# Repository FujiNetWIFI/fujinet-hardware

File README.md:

# FujiNet Hardware

Hardware design files for FujiNet Retro Computer WiFi Adapter

# License

This project is released under the CERN OHL v2.0.

# Notice

Licensees must place a link to the FujiNet project github site, github.com/FujiNetWIFI OR fujinetwifi.github.io, on any product produced using these designs. Using the PCB silk screen layer is recommended for the link and is already provided on released designs.

# Certification

FujiNet hardware is certified open source by [OSHWA](https://oshwa.org). Certification details are available in the [certification directory](https://certification.oshwa.org/us000651.html) under the UID US000651.

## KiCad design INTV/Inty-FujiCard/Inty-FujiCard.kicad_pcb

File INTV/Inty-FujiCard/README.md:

# Inty-FujiCard

FujiNet for the Intellivision, on one cartridge: Yannick Erb's production design (EasyEDA project PINTY-FUJI-CARD, PCB v1.1, 2026-11-04), converted to KiCad in the structure of the other console bring-ups.
- **RP2354A:** serves the CP1610's bus (`fujinet-firmware/pico/intellivision`, board `fujicard`). AD0-15, MSYNC, BDIR, BC1 and BC2 go straight from the edge to its GPIOs.
- **ESP32-S3:** the FujiNet (`fujiversal-intv`) and the RP's USB host, on the same board.
- **Also on the board:** a microSD, an SK6805 status LED, and a USB-C with a CP2102N bridge for flashing and power.

`Original/` holds Yannick's files exactly as he sent them: the EasyEDA PCB (JSON), an Altium ASCII export, his gerbers and drills, BOM and pick-and-place. Everything else is generated from them (`tools/`).

**Status (2026-11-05): converted, every gate passing. The copper, masks, paste, drills and silkscreen equal Yannick's gerbers; his BOM and placements are carried over unchanged.**
- **Board:** 2 layers, 58.2 x 60.0 mm, 1.6 mm. Yannick's layout, unchanged. His EasyEDA files had no schematic: the schematic here is drawn from the board's netlist.
- **Firmware:** the netlist matches `fujicard.h` and `fujiversal-intv.h` on every bus and S3 pin. The mismatches are listed under *Firmware*.
- **Before ordering:** see *Known limits / review*. The paste layers open the gold fingers, and three lines were out of stock on 2026-11-05.

| Check (2026-11-05) | Result |
|---|---|
| `tools/audit/gerber_equiv.py`: our PCBWay zip against Yannick's gerber zip, rasterised at 40 px/mm and XOR-ed | F.Cu, B.Cu, F/B.Mask, F/B.Paste, outline: identical (nothing left after a 50 um opening); silkscreen graphics identical, all 42 visible texts centred within 0.05 mm of his; 160 plated and 6 unplated holes, all his |
| `tools/board_netlist.py --check`: `tools/design.py` against the board's own netlist | 76 nets, 78 parts, every unconnected pad NC; Yannick's net names kept |
| Drawing checks (`gen_sch.py`) and netlist parity (kicad-cli netlist against `design.py`, names included) | every sheet wired; 0 crossings on 4 sheets, 1 on `usb` (esptool's auto-program pair); 76 / 76 nets |
| KiCad ERC, all severities | 0 errors, 0 warnings |
| `tools/check_nets.py`: the netlist against `fujicard.h`, `pintycard.h`, `fujiversal-intv.h` (fujinet-firmware `origin/master`) | 72 checks, 0 failed; 8 NOTE lines (*Firmware*) |
| `tools/sync_board.py`: schematic -> board, names and fields only | copper hash unchanged |
| `tools/audit/check_drc.py`: KiCad DRC + schematic parity on the saved fills (kicad-cli; again through the KiCad MCP) | 0 errors, 0 unconnected, 0 parity issues; 101 warnings, all from Yannick's footprints (*Design rules*) |
| `tools/audit/check_fab.py`: the JLCPCB / PCBWay packages against his BOM and pick-and-place | BOM = his 31 lines / 70 parts with his LCSC codes and MPNs; CPL = his placements (worst 0.005 mm, every rotation); the zips |

## What the conversion changed

KiCad 10.0.8's EasyEDA importer (`pcbnew.PCB_IO_MGR.EASYEDA`) reads the JSON. `tools/convert.py` keeps what it gets right and fixes what it gets wrong. Each fix is proven against Yannick's gerbers:
1. **The GND pours' holes.** EasyEDA stores each pour's fill with its clearance holes, and the importer drops the holes. As imported, the B.Cu pour covered 31 signal tracks (230 mm2 of copper that is not on his board), and the F.Cu pour filled 129 clearances. The fills are rebuilt from the JSON.
2. **Paste and silkscreen drawn inside footprints.** The importer drops these shapes: 142 paste openings and 13 silkscreen marks (polarity bars, pin-1 dots). Their pads carry EasyEDA's "no paste of its own" value (-393.7 x 10 mil, imported as a -100 mm margin). They are restored; those 138 pads have no F.Paste of their own.
3. **Text.** The importer shows every value and reference; the JSON hides all values and 40 references, and its visibility flags are applied. KiCad anchors each text where EasyEDA's starts, so every text sat 0.2-1.4 mm off; each is moved so its strokes are centred on EasyEDA's. The font is KiCad's.
4. **3D models.** The importer offsets each EasyEDA model as if its origin were its solids' box centre and bottom. EasyEDA places them by that box, and several are not centred on their origin: the microSD socket sat 29 mm away and under the board. `tools/fetch_models.py` normalises each model (`3d/README.md`).
5. **Solid regions** (the 386 teardrops and copper shapes) become filled copper polygons with their nets, not zones, so no refill can redraw them. Two that EasyEDA drew twice are kept once.
6. **Housekeeping:**
   - KiCad's own layer names.
   - The 23 footprints go into `Inty-FujiCard.pretty`.
   - The designators KiCad cannot annotate are numbered (table below).
   - The 3D models are bundled.
   - The crystal's no-fill keep-out is 10 um smaller: EasyEDA's pour touched it.
   - UUIDs are fixed, so a rerun diffs clean.

**Never refill the zones.** The two GND pours are EasyEDA's own fills. A refill (B in pcbnew, `--refill-zones`, `--check-zones`) replaces them with KiCad's. `tools/audit/gerber_equiv.py` would then report the difference.

| Yannick's | Here | | Yannick's | Here |
|---|---|---|---|---|
| BOOT | SW1 | | GND (test pad) | TP1 |
| RESET | SW2 | | TX | TP2 |
| RP-BOOT | SW3 | | RX | TP3 |
| RP-RUN | SW4 | | SWD | TP4 |
| LED | D6 | | SWCLK | TP5 |
| USB | J1 | | Hole_gge2670 / 2700 | H1 / H2 |

The silkscreen still reads BOOT, RESET, RP-BOOT, RP-RUN, LED, USB, GND, TX, RX, SWD and SWCLK: each label is kept as board text, grouped with its part. Every other designator is his.

## Sheets

Drawn with the FujiNet-ColecoVision / O2 / Arcadia toolkit:
- **Wires only:** every connection on a sheet is a wire.
- **Rails:** rails are power symbols (`GND`, `VSYS`, `VBUS`, `VIN`, `3V3`, `1V1`).
- **Between sheets:** sheets join only through hierarchical labels, wired on the root's block diagram.

| Page | Sheet | Contents |
|---|---|---|
| 1 | root | the block diagram: rp-core <-> fujinet (USB_DP / USB_DM, RUN_CTL, BOOTSEL_CTL), fujinet <-> usb (S3_TXD / S3_RXD, S3_EN, S3_IO0); notes |
| 2 | `cart-bus` | the 44-finger edge and the RP2354A's GPIO unit row for row; the console reset (GP20, R13, Q1), the ECS audio (GP28, R5), the TX / RX pads |
| 3 | `rp-core` | the RP2354A's core unit: its supply capacitors, core regulator (L1, R6 / C19), crystal, USB 27R pair, QSPI_SS / RP-BOOT / Q3, RUN / RP-RUN / Q4, SWD pads |
| 4 | `fujinet` | ESP32-S3-WROOM-1-N16R8, EN RC and RESET, BOOT, microSD with the YC158 pull-ups, SK6805 |
| 5 | `usb` | USB-C, ESD5Z diodes, CP2102N, esptool's auto-program pair (UMH3N) |
| 6 | `power` | the SS34 diode-OR (VSYS, VBUS -> VIN), the AP63203 buck (3V3), PWR_FLAGs, the holes |

## Edge connector

44 contacts in two rows of 22 at 2.54 mm. Yannick's footprint numbers them A1-A22 on the component face and B1-B22 behind, left to right, seen from the component face with the contacts down. Finger A(k) is INTV pin 46 - 2k, and B(k) is pin 45 - 2k: even pins in front, odd behind.

| Pin | Finger | Signal | Goes to | Pin | Finger | Signal | Goes to |
|---|---|---|---|---|---|---|---|
| 1 | B22 | GND | GND | 2 | A22 | NC | - |
| 3 | B21 | /MSYNC | GP21 | 4 | A21 | NC | - |
| 5 | B20 | D7 | GP7 | 6 | A20 | EXT_AUDIO | R5 from GP28 |
| 7 | B19 | D8 | GP8 | 8 | A19 | GND | GND |
| 9 | B18 | D6 | GP6 | 10 | A18 | GND | GND |
| 11 | B17 | D9 | GP9 | 12 | A17 | /RESET | Q1 (GP20 via R13) |
| 13 | B16 | D5 | GP5 | 14 | A16 | NC | - |
| 15 | B15 | D10 | GP10 | 16 | A15 | NC | - |
| 17 | B14 | D4 | GP4 | 18 | A14 | NC | - |
| 19 | B13 | D11 | GP11 | 20 | A13 | GND | GND |
| 21 | B12 | D3 | GP3 | 22 | A12 | GND | GND |
| 23 | B11 | D12 | GP12 | 24 | A11 | GND | GND |
| 25 | B10 | D13 | GP13 | 26 | A10 | GND | GND |
| 27 | B9 | D2 | GP2 | 28 | A9 | GND | GND |
| 29 | B8 | D14 | GP14 | 30 | A8 | NC | - |
| 31 | B7 | D1 | GP1 | 32 | A7 | PASS_A | joined to pin 42 |
| 33 | B6 | D0 | GP0 | 34 | A6 | PASS_B | joined to pin 40 |
| 35 | B5 | D15 | GP15 | 36 | A5 | PASS_C | joined to pin 38 |
| 37 | B4 | BDIR | GP22 | 38 | A4 | PASS_C | joined to pin 36 |
| 39 | B3 | BC2 | GP27 | 40 | A3 | PASS_B | joined to pin 34 |
| 41 | B2 | BC1 | GP26 | 42 | A2 | PASS_A | joined to pin 32 |
| 43 | B1 | +5V | VSYS -> D1 | 44 | A1 | GND | GND |

The pinout is the attic FujiNet-INTV-Rev0's edge, traced from the PiNTY CARD's gerbers. The firmware's bus map agrees on every finger (`tools/check_nets.py` keeps its own copy of both).

## RP2354A pin map

| GPIO | Net | Goes to |
|---|---|---|
| 0-15 | GPIO00-15 | the edge's D0-D15 (`MI_AD0_PIN` 0), straight |
| 16 / 17 | GPIO16 / 17 | test pads TP2 (silk TX) / TP3 (silk RX) |
| 18, 19, 23, 24, 25, 29 | - | not connected |
| 20 | GPIO20 | R13 -> Q1: high pulls the console's /RESET (pin 12) low (`MI_RST_PIN`) |
| 21 / 22 | GPIO21 / 22 | MSYNC / BDIR, straight |
| 26 / 27 | GPIO26 / 27 | BC1 / BC2, straight |
| 28 | PWM | R5 1k -> EXT_AUDIO (pin 6, the ECS audio; `pintycard.h` `MI_AUDIO_PIN`) |
| QSPI | QSPI_SS | the BOOTSEL strap (R12 10k up; RP-BOOT / Q3 through R11 1k); the flash is in the package, the other QSPI pins are not connected |
| USB | USB_D+ / USB_D- | 27R -> the ESP32-S3's IO20 / IO19 (the S3 is the host) |
| RUN | RUN | R14 10k up; RP-RUN (SW4); Q4 |

## ESP32-S3 pin map

`include/pinmap/fujiversal-intv.h`:

| S3 pin | Net | Goes to |
|---|---|---|
| IO19 / IO20 | USB_DM / USB_DP | the RP2354A's USB through its 27R |
| IO38 / 39 / 40 / 41 | SD_MOSI / SCK / MISO / CS | microSD (SPI); 10k pull-ups (RN1) on CS, DO, DI, DAT1, DAT2; card detect not connected |
| IO48 | LED_STRIP | 330R -> SK6805-EC20 (on 3V3) |
| TXD0 / RXD0 | S3_TXD / S3_RXD | CP2102N RXD / TXD |
| IO4 / IO5 | RUN_CTL / BOOTSEL_CTL | 1k -> Q4 / Q3: high pulls the RP's RUN / QSPI_SS low |
| EN / IO0 | S3_EN / S3_IO0 | 10k / 1 uF and RESET (SW2); BOOT (SW1), 100 nF, 10k up; the auto-program pair |

## Power

| Rail | Source | Feeds |
|---|---|---|
| `VSYS` | edge pin 43, the console's +5V | D1 (SS34) -> VIN |
| `VBUS` | USB-C | D2 (SS34) -> VIN; the CP2102N's VBUS sense (22.1k / 47.5k) |
| `VIN` | the higher of the two, less a Schottky drop | C29 100 uF, C25 10 uF; the AP63203 |
| `3V3` | AP63203, 3.3 V / 2 A buck (4.7 uH) | everything: the RP2354A (IOVDD, VREG_VIN, ADC, USB, QSPI), the ESP32-S3, the CP2102N, the microSD, the SK6805 |
| `1V1` | the RP2354A's core regulator (L1 3.3 uH) | the RP's DVDD |

Neither source can back-feed the other: a cart on USB never powers a console that is off.

## Design rules

The Board Setup minimums (`tools/rules.json`) are the lowest values Yannick's copper needs. `Inty-FujiCard.kicad_dru` holds everything else to JLCPCB's standard 1-2 layer figures (0.127 mm space, 0.45 / 0.2 mm via, 0.125 mm ring, 0.3 mm to the edge). The measured exceptions:
- **Spacing:** 6 spots at 0.107-0.121 mm, in the RP2354A's and the CP2102N's fan-out (QFNs at 0.4 / 0.5 mm pitch). His EasyEDA rule there is 0.1016 mm.
- **Vias:** 151 are 0.457 / 0.254 mm, a 0.1015 mm ring (EasyEDA's 18 / 10 mil). The other 5 are 0.62 / 0.31 mm.
- **Hole clearance:** the USB-C's own pads sit 0.171-0.213 mm from its locating pegs (the connector's footprint). One B.Cu track (GPIO09) passes 0.243 mm from GPIO08's via.
- **Edge clearance:** the two GND pours stop 0.259 mm from the outline's centre line.
- **Placement:** C9, C10, C13 and C19 are inside the RP2354A's courtyard, and R3 overlaps L1's (EasyEDA courtyards).
- **Pad 23:** the CP2102N's GND pad 23 reaches the pour by one spoke.

The 101 DRC warnings are all his footprints' (`tools/audit/check_drc.py` fails on any other):
- 47 `lib_footprint_mismatch`: EasyEDA placed each instance with its own 0.1-0.2 um rounding and fab-text angle; the library holds the first.
- 39 `silk_overlap`: polarity bars and pin-1 dots over the parts' own outlines.
- 10 `silk_edge_clearance`: the USB-C, the S3 and the microSD outlines at the board edge.
- 4 `silk_over_copper`: the USB-C outline over its shell legs.
- 1 `track_dangling`: a zero-length 3V3 dot on B.Cu, which is in his gerbers too.

## Parts

Every part is Yannick's, with his LCSC code (`Inty-FujiCard-BOM.csv` has MPN, manufacturer and LCSC for every line). Run `python3 tools/audit/sourcing.py` on order day.

**Stock (2026-11-05, `docs/sourcing.md`):** 31 lines, about USD 11.59 of parts per board. Three lines are short at JLCPCB:
- **U1 RP2354A** (C41378174): JLCPCB 0, LCSC 0.
- **U2 AP63203WU-7** (C780769): JLCPCB 0, LCSC 0.
- **RN1 YC158TJR-0710KL** (C309679): JLCPCB 1, LCSC 0.

Consign them, use JLC Global Sourcing, or order from PCBWay, which sources by MPN. **C29** (Lelon VE-101M1ATR-0505, C134722) is marked `stop_product` at LCSC, with 408 left at JLCPCB. Any substitute is Yannick's call.

## Ordering

- **JLCPCB:** `exports/jlcpcb/ORDER-JLCPCB.md`. `BOM-JLCPCB.csv` and `CPL-JLCPCB.csv` equal his files: his footprints are LCSC's own, so no rotation table applies. The zip carries the order-number text on the back silkscreen.
- **PCBWay:** `exports/pcbway/ORDER-PCBWay.md`, turnkey by MPN (`BOM-PCBWay.csv`), `Centroid-PCBWay.csv`, `Assembly-top.pdf`.

Yannick's files give no order options. The finish, hard-gold fingers and bevel in the ORDER files are the house recommendation for a cartridge edge: confirm them with him.

## Firmware (not changed here)

`tools/check_nets.py` reports these as NOTE lines:
1. **`fujicard.h` names pins this board does not connect:**
   - `MI_LED_PIN` 25 (no RP LED here).
   - `MI_DBG_UART_TX_PIN` 24: the TX / RX pads are GP16 / GP17.
   - `FUJI_SELFTEST_TRIGGER_PIN` 23.
   
   Its comment says "No PCB pin map is committed yet": this board is one.
2. **RUN / BOOTSEL polarity.** The S3 reaches the RP's RUN and QSPI_SS through NPNs (Q4, Q3), so IO4 / IO5 must be driven **high** to assert. `fnPicoUpdater::forceBootselViaPins()` drives them low (for a direct 1k link), so that recovery path does nothing on this board. The normal path, the USB mailbox doorbell, is unaffected.
3. **ECS audio.** GP28 is wired to EXT_AUDIO as `pintycard.h` has it (`MI_AUDIO_PIN` 28). `fujicard.h` defines no audio pin, and `fujicard.cmake` has `CONFIG_ECS_AUDIO` off.

## Known limits / review

- **Paste on the gold fingers.** His F.Paste and B.Paste open all 44 fingers, and our gerbers equal his. Ask the fab to keep the fingers out of the stencil, or confirm with Yannick how his boards were built.
- **BC1 / BC2 on GP26 / GP27.** These are the RP2350's ADC pins, not 5 V tolerant (GP0-25 are). They meet the console's lines directly, as on the PiNTY CARD.
- **Fab limits.** The spacing and via-ring exceptions above are below JLCPCB's standard 2-layer figures. Check the quote's DFM report.
- **The ESP32-S3 overhangs** the board's top edge by about 6.2 mm (the antenna). The shell must allow for it.
- **Designators.** U5 is the crystal: Yannick's designator, kept.

## Bring-up checklist

1. **Rails, with no console:** USB-C only. Check 3V3 (C4 / C22) and 1V1 (C17). The SK6805 lights.
2. **First flash of the RP:** SWD on TP4 (SWDIO), TP5 (SWCLK) and TP1 (GND), with a Raspberry Pi Debug Probe. Or hold RP-BOOT while pressing RP-RUN for the USB boot ROM; its USB reaches only the S3.
3. **The S3:** flash over the USB-C. The CP2102N and the auto-program pair drive EN and IO0.
4. **In a console, no USB:** measure VIN and 3V3 under WiFi load, then CONFIG on the TV.
5. **Console off with USB on:** confirm D1 blocks: VSYS stays at 0 V.

## Regenerating

You need KiCad 10 and Python 3 with numpy, scipy and pycairo. `check_nets.py` reads fujinet-firmware from `$FUJINET_FIRMWARE` (default `~/Workspace/fujinet-firmware`) at `$FUJINET_FIRMWARE_REF` (default `origin/master`).

```sh
tools/build_all.sh                 # schematic, ERC, check_nets, sync, DRC, exports, the fab gates (keeps the board)
CONVERT=1 tools/build_all.sh       # first re-converts Original/PCB_*.json (tools/convert.py) and its netlist
python3 tools/fetch_models.py      # re-fetch the EasyEDA 3D models into 3d/ (network)
python3 tools/audit/sourcing.py    # stock at JLCPCB and LCSC -> docs/sourcing.md (network)
```

Each source file has one job:
- `tools/convert.py`: the board and footprints, from `Original/`.
- `tools/design.py`: the circuit as written out.
- `tools/sch_layout.py`: the drawing.

Edit those, never the KiCad files.

## Provenance and licence

- **The design:** Yannick Erb, PINTY-FUJI-CARD v1.1 (EasyEDA, 2026-11-04). It grows out of his PiNTY CARD (with gtortone), which is CERN-OHL-W-2.0. **His files state no licence for this board: confirm one with him before publishing it.**
- **The conversion:**
  - `tools/`; the drawing toolkit and the serializer from FujiNet-ColecoVision / O2 / Arcadia Rev0.
  - `tools/gen_sch.py`'s RP2354A core unit and S3 symbol from FujiNet-ColecoVision Rev0.
  - The edge pinout from the attic FujiNet-INTV-Rev0.
- **The pin maps:** `fujinet-firmware` `pico/intellivision` and `include/pinmap/fujiversal-intv.h`.
- **Symbols:**
  - Official KiCad libraries (CC-BY-SA 4.0 with exception).
  - Project symbols for the edge, the RP2354A in two units, the ESP32-S3 by function, Yannick's USB-C, microSD, YC158 array and SK6805-EC20, each numbered as his footprints are.
- **Footprints:** Yannick's (LCSC / EasyEDA), as on the board.
- **3D models:** `3d/README.md`.

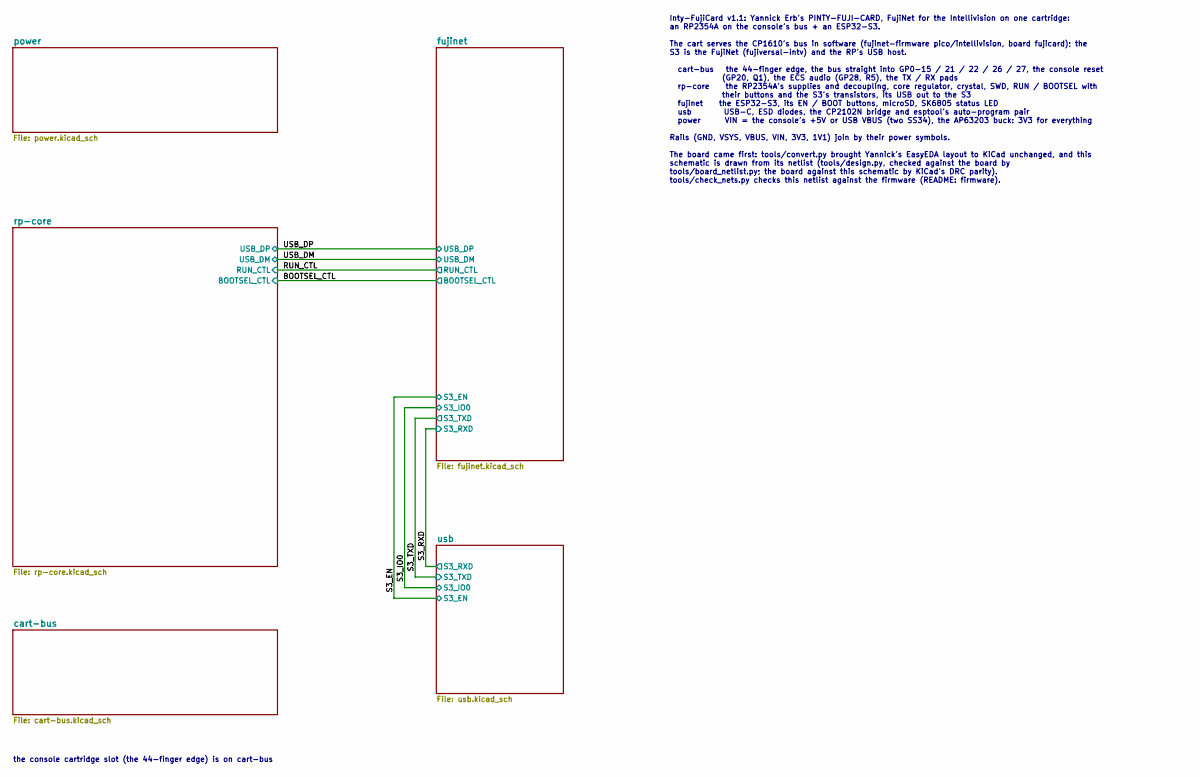
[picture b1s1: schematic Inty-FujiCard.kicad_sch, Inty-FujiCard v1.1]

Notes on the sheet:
the console cartridge slot (the 44-finger edge) is on cart-bus
Inty-FujiCard v1.1: Yannick Erb's PINTY-FUJI-CARD, FujiNet for the Intellivision on one cartridge: an RP2354A on the console's bus + an ESP32-S3. The cart serves the CP1610's bus in software (fujinet-firmware pico/intellivision, board fujicard); the S3 is the FujiNet (fujiversal-intv) and the RP's 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

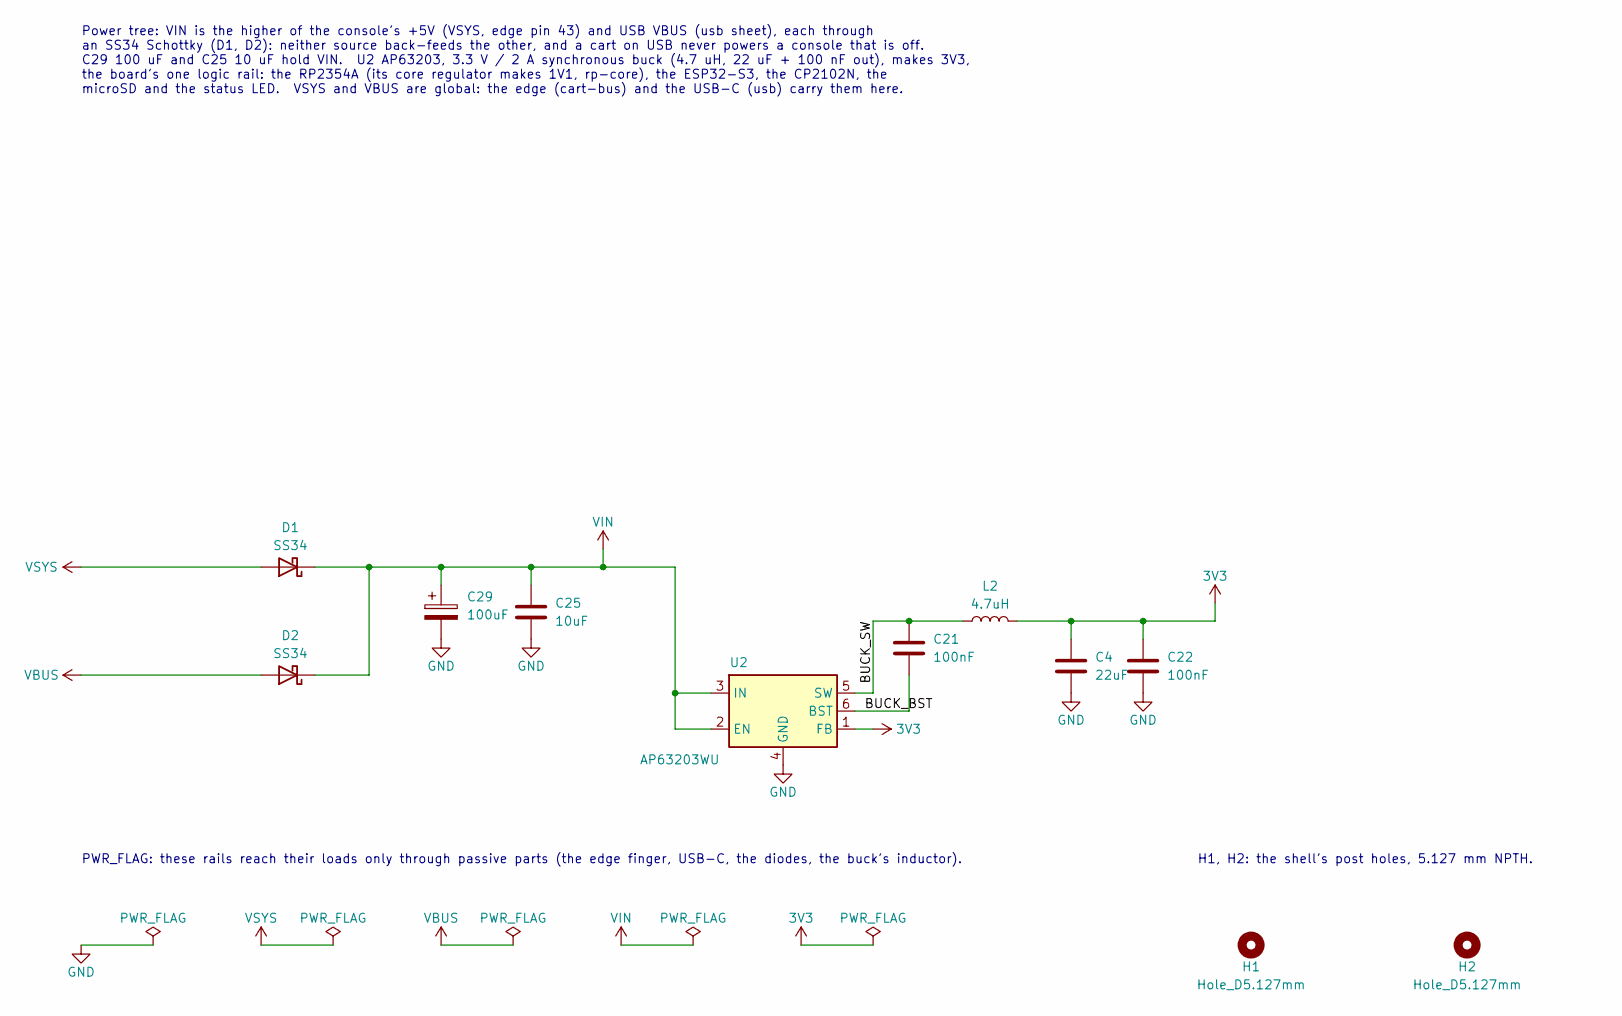
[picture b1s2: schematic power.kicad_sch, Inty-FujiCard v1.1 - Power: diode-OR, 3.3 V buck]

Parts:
C4: 22uF; C0603; MPN CL10A226MQ8NRNC; LCSC C59461
C21, C22: 100nF; C0402; MPN CL05B104KO5NNNC; LCSC C1525
C25: 10uF; C0603; MPN CL10A106KP8NNNC; LCSC C19702
C29: 100uF; CAP-SMD_BD5.0-L5.3-W5.3-RD; MPN VE-101M1ATR-0505; LCSC C134722
D1, D2: SS34; SMA_L4.3-W2.6-LS5.2-RD; MPN SS34; LCSC C8678
H1, H2: Hole_D5.127mm; Hole_D5.127mm_NPTH
L2: 4.7uH; IND-SMD_L3.0-W3.0-1; MPN YNR3015-4R7M; LCSC C340361
U2: AP63203WU; TSOT-26_L2.9-W1.6-P0.95-LS2.8-BL; MPN AP63203WU-7; LCSC C780769

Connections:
3V3: C4.2, C22.2, L2.2, U2.1 (FB); also elsewhere on the board
/power/BUCK_BST: C21.2, U2.6 (BST)
/power/BUCK_SW: C21.1, L2.1, U2.5 (SW)
GND: C4.1, C22.1, C25.1, C29.2, U2.4 (GND); also elsewhere on the board
VBUS: D2.2 (A); also elsewhere on the board
VIN: C25.2, C29.1, D1.1 (K), D2.1 (K), U2.2 (EN), U2.3 (IN)
VSYS: D1.2 (A); also elsewhere on the board

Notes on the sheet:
PWR_FLAG: these rails reach their loads only through passive parts (the edge finger, USB-C, the diodes, the buck's inductor).
H1, H2: the shell's post holes, 5.127 mm NPTH.
Power tree: VIN is the higher of the console's +5V (VSYS, edge pin 43) and USB VBUS (usb sheet), each through an SS34 Schottky (D1, D2): neither source back-feeds the other, and a cart on USB never powers a console that is off. C29 100 uF and C25 10 uF hold VIN. U2 AP63203, 3.3 V / 2 A synchronous 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

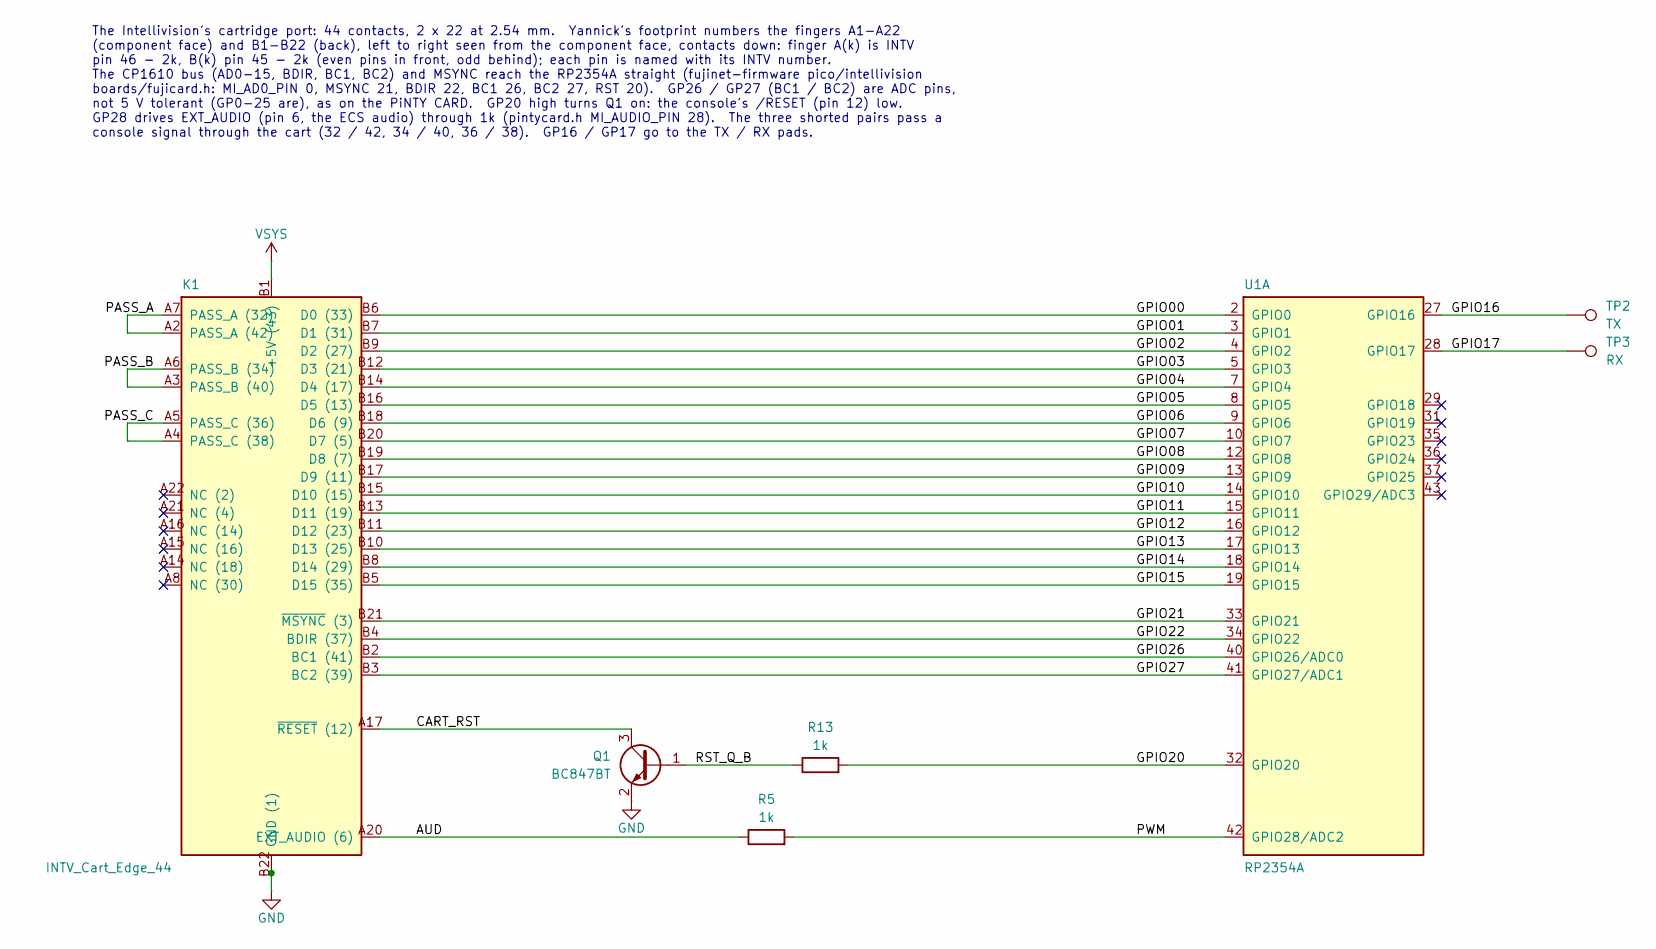
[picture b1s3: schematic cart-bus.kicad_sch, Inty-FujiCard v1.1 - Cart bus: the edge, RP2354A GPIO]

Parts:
K1: INTV_Cart_Edge_44; PCB_EDGE_CONNECTOR_22X2
Q1: BC847BT; SOT-523-3_L1.6-W0.8-P1.00-LS1.6-BR; MPN BC847BT; LCSC C5186022
R5, R13: 1k; R0402; MPN 0402WGF1001TCE; LCSC C11702
TP2: TX; TESTPOINT_PAD_D1.5MM
TP3: RX; TESTPOINT_PAD_D1.5MM
U1: RP2354A; QFN-60_L7.0-W7.0-P0.40-TL-EP3.4; MPN RP2354A; LCSC C41378174

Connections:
/cart-bus/AUD: K1.A20 (EXT_AUDIO (6)), R5.1
/cart-bus/CART_RST: K1.A17 (~RESET (12)), Q1.3 (C)
/cart-bus/GPIO00: K1.B6 (D0 (33)), U1.2 (GPIO0)
/cart-bus/GPIO01: K1.B7 (D1 (31)), U1.3 (GPIO1)
/cart-bus/GPIO02: K1.B9 (D2 (27)), U1.4 (GPIO2)
/cart-bus/GPIO03: K1.B12 (D3 (21)), U1.5 (GPIO3)
/cart-bus/GPIO04: K1.B14 (D4 (17)), U1.7 (GPIO4)
/cart-bus/GPIO05: K1.B16 (D5 (13)), U1.8 (GPIO5)
/cart-bus/GPIO06: K1.B18 (D6 (9)), U1.9 (GPIO6)
/cart-bus/GPIO07: K1.B20 (D7 (5)), U1.10 (GPIO7)
/cart-bus/GPIO08: K1.B19 (D8 (7)), U1.12 (GPIO8)
/cart-bus/GPIO09: K1.B17 (D9 (11)), U1.13 (GPIO9)
/cart-bus/GPIO10: K1.B15 (D10 (15)), U1.14 (GPIO10)
/cart-bus/GPIO11: K1.B13 (D11 (19)), U1.15 (GPIO11)
/cart-bus/GPIO12: K1.B11 (D12 (23)), U1.16 (GPIO12)
/cart-bus/GPIO13: K1.B10 (D13 (25)), U1.17 (GPIO13)
/cart-bus/GPIO14: K1.B8 (D14 (29)), U1.18 (GPIO14)
/cart-bus/GPIO15: K1.B5 (D15 (35)), U1.19 (GPIO15)
/cart-bus/GPIO16: TP2.1, U1.27 (GPIO16)
/cart-bus/GPIO17: TP3.1, U1.28 (GPIO17)
/cart-bus/GPIO20: R13.2, U1.32 (GPIO20)
/cart-bus/GPIO21: K1.B21 (~MSYNC (3)), U1.33 (GPIO21)
/cart-bus/GPIO22: K1.B4 (BDIR (37)), U1.34 (GPIO22)
/cart-bus/GPIO26: K1.B2 (BC1 (41)), U1.40 (GPIO26/ADC0)
/cart-bus/GPIO27: K1.B3 (BC2 (39)), U1.41 (GPIO27/ADC1)
/cart-bus/PASS_A: K1.A2 (PASS_A (42)), K1.A7 (PASS_A (32))
/cart-bus/PASS_B: K1.A3 (PASS_B (40)), K1.A6 (PASS_B (34))
/cart-bus/PASS_C: K1.A4 (PASS_C (38)), K1.A5 (PASS_C (36))
/cart-bus/PWM: R5.2, U1.42 (GPIO28/ADC2)
/cart-bus/RST_Q_B: Q1.1 (B), R13.1
GND: K1.A1 (GND (44)), K1.A9 (GND (28)), K1.A10 (GND (26)), K1.A11 (GND (24)), K1.A12 (GND (22)), K1.A13 (GND (20)), K1.A18 (GND (10)), K1.A19 (GND (8)), K1.B22 (GND (1)), Q1.2 (E); also elsewhere on the board
VSYS: K1.B1 (+5V (43)); also elsewhere on the board

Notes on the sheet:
The Intellivision's cartridge port: 44 contacts, 2 x 22 at 2.54 mm. Yannick's footprint numbers the fingers A1-A22 (component face) and B1-B22 (back), left to right seen from the component face, contacts down: finger A(k) is INTV pin 46 - 2k, B(k) pin 45 - 2k (even pins in front, odd behind); each 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

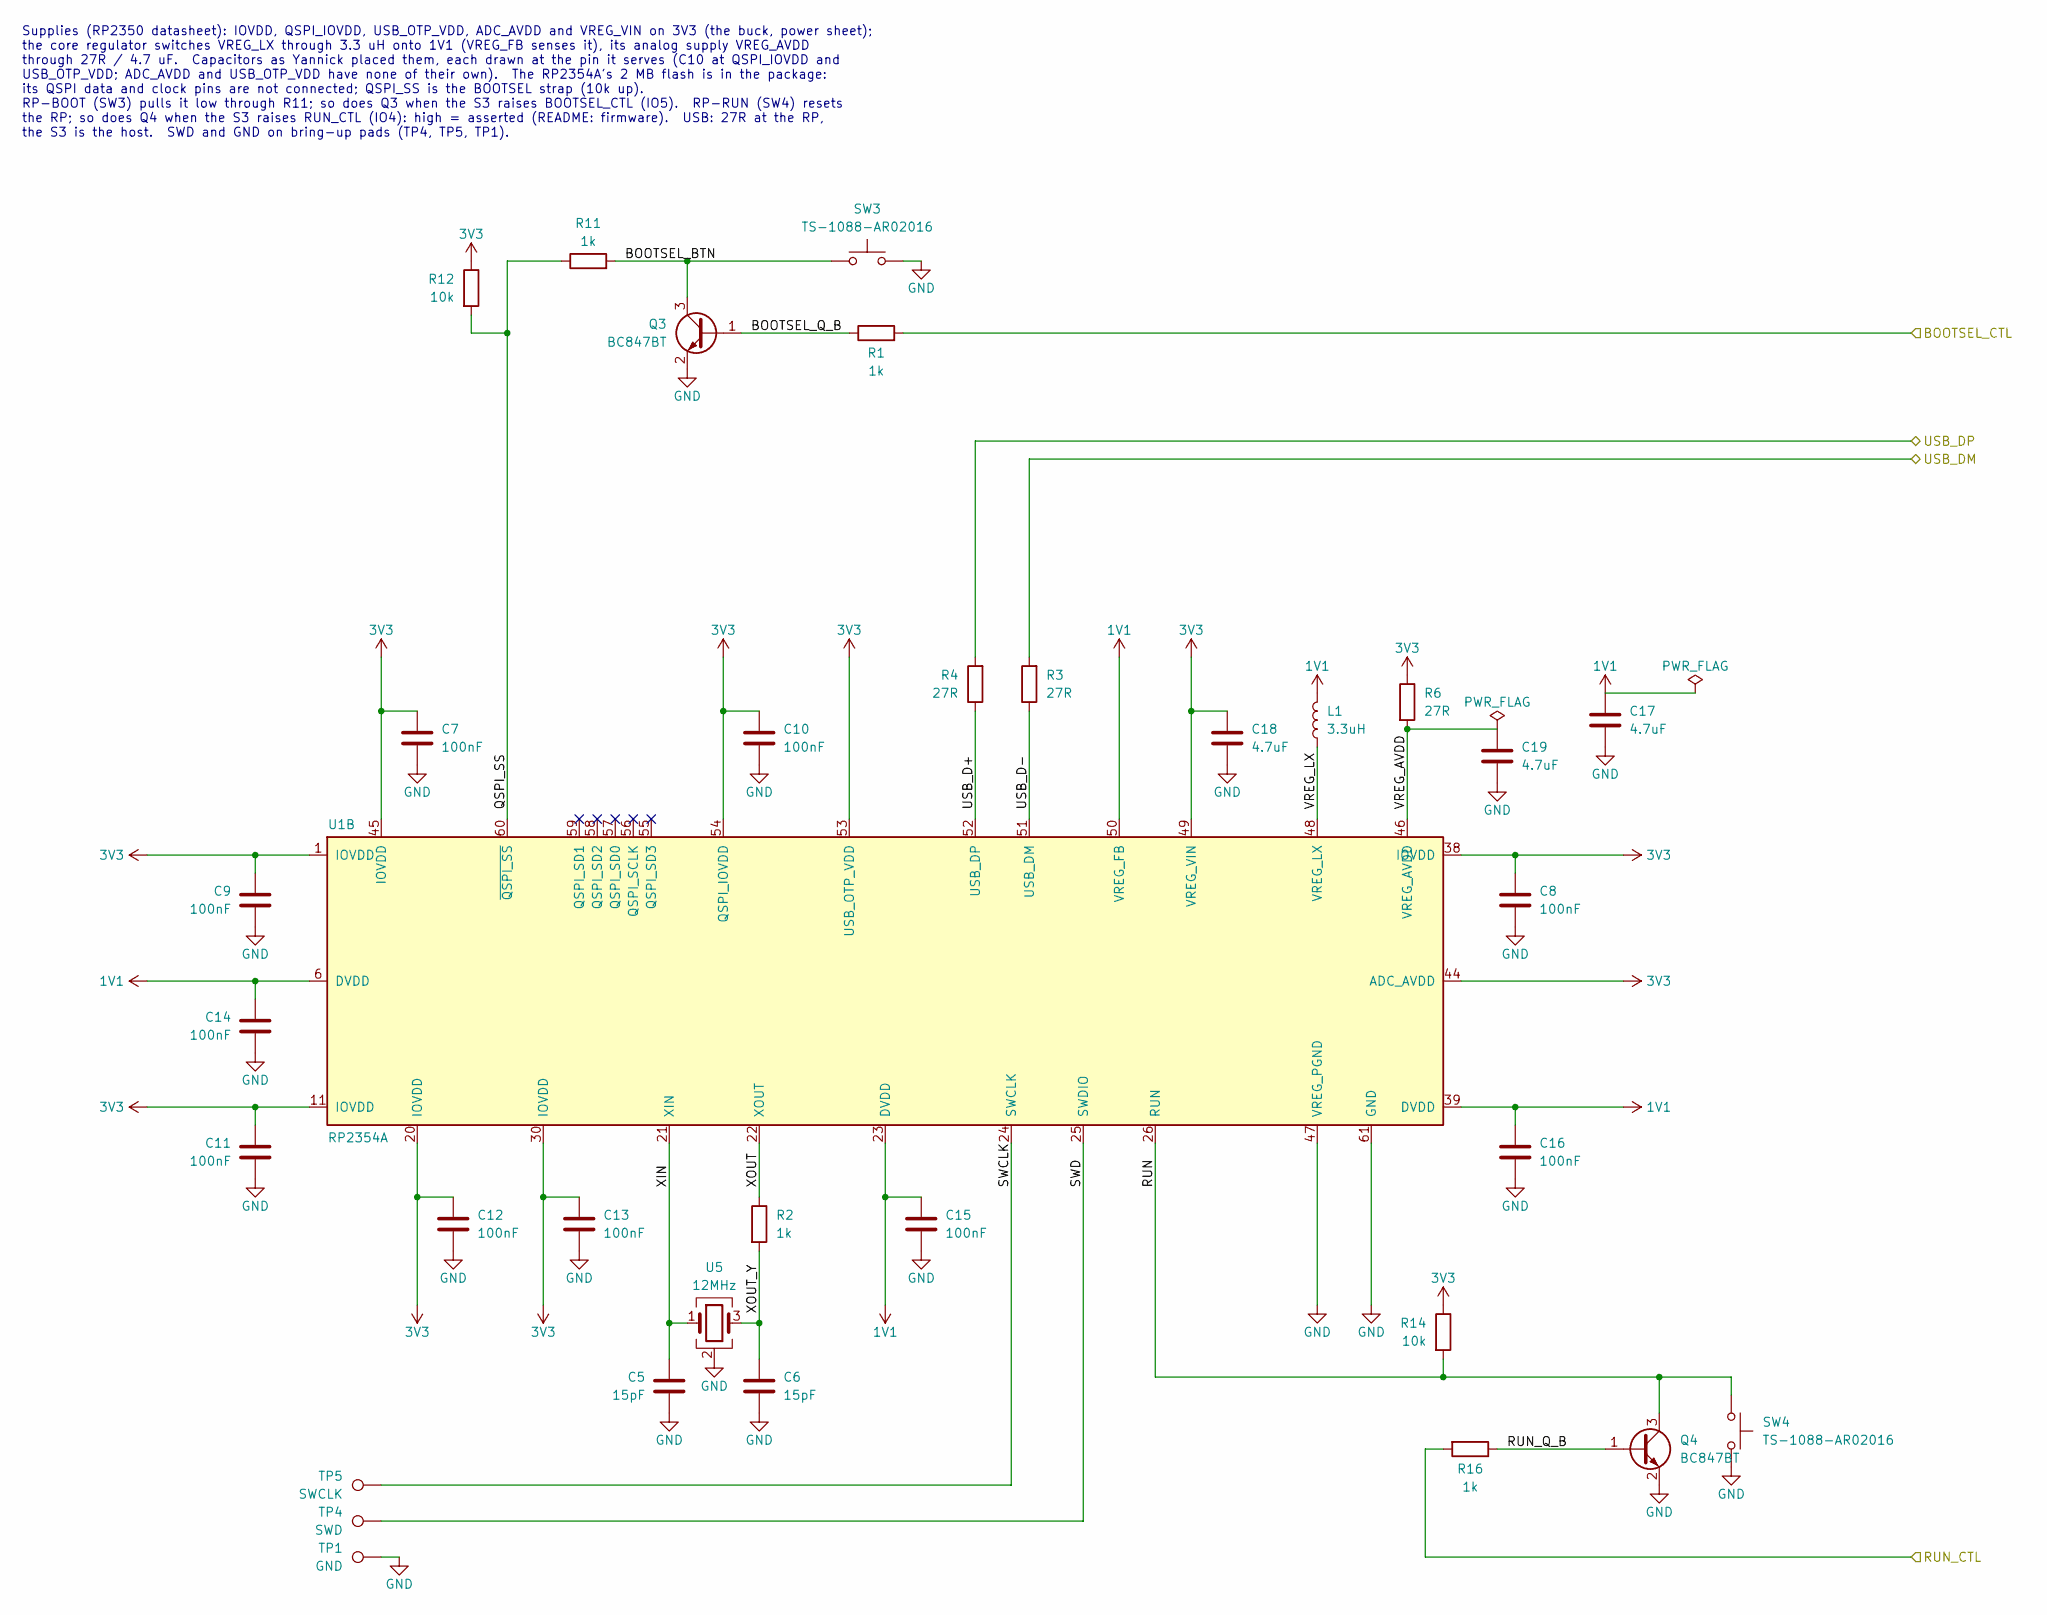
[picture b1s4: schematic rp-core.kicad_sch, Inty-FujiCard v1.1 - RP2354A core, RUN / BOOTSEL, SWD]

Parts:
C5, C6: 15pF; C0402; MPN 0402CG150J500NT; LCSC C1548
C7, C8, C9, C10, C11, C12, C13, C14, C15, C16: 100nF; C0402; MPN CL05B104KO5NNNC; LCSC C1525
C17, C18: 4.7uF; C0603; MPN CL10A475KO8NNNC; LCSC C19666
C19: 4.7uF; C0402; MPN CL05A475MP5NRNC; LCSC C23733
L1: 3.3uH; IND-SMD_L2.0-W1.6_AOTA-B201610S3R3-101-T; MPN AOTA-B201610S3R3-101-T; LCSC C42411119
Q3, Q4: BC847BT; SOT-523-3_L1.6-W0.8-P1.00-LS1.6-BR; MPN BC847BT; LCSC C5186022
R1, R2, R11, R16: 1k; R0402; MPN 0402WGF1001TCE; LCSC C11702
R3, R4, R6: 27R; R0402; MPN 0402WGF270JTCE; LCSC C25100
R12, R14: 10k; R0402; MPN 0402WGF1002TCE; LCSC C25744
SW3, SW4: TS-1088-AR02016; SW-SMD_L3.9-W3.0-P4.45; MPN TS-1088-AR02016; LCSC C720477
TP1: GND; TESTPOINT_PAD_D1.5MM
TP4: SWD; TESTPOINT_PAD_D1.5MM
TP5: SWCLK; TESTPOINT_PAD_D1.5MM
U1: RP2354A; QFN-60_L7.0-W7.0-P0.40-TL-EP3.4; MPN RP2354A; LCSC C41378174
U5: 12MHz; CRYSTAL-SMD_4P-L3.2-W2.5-BL; MPN ABM8-272-T3; LCSC C20625731

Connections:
1V1: C14.2, C15.2, C16.2, C17.2, L1.2, U1.6 (DVDD), U1.23 (DVDD), U1.39 (DVDD), U1.50 (VREG_FB)
3V3: C7.2, C8.2, C9.2, C10.2, C11.2, C12.2, C13.2, C18.2, R6.1, R12.1, R14.1, U1.1 (IOVDD), U1.11 (IOVDD), U1.20 (IOVDD), U1.30 (IOVDD), U1.38 (IOVDD), U1.44 (ADC_AVDD), U1.45 (IOVDD), U1.49 (VREG_VIN), U1.53 (USB_OTP_VDD), U1.54 (QSPI_IOVDD); also elsewhere on the board
/BOOTSEL_CTL: R1.2; also elsewhere on the board
/RUN_CTL: R16.2; also elsewhere on the board
/USB_DM: R3.2; also elsewhere on the board
/USB_DP: R4.2; also elsewhere on the board
/rp-core/BOOTSEL_BTN: Q3.3 (C), R11.2, SW3.1
/rp-core/BOOTSEL_Q_B: Q3.1 (B), R1.1
/rp-core/QSPI_SS: R11.1, R12.2, U1.60 (~QSPI_SS)
/rp-core/RUN: Q4.3 (C), R14.2, SW4.1, U1.26 (RUN)
/rp-core/RUN_Q_B: Q4.1 (B), R16.1
/rp-core/SWCLK: TP5.1, U1.24 (SWCLK)
/rp-core/SWD: TP4.1, U1.25 (SWDIO)
/rp-core/USB_D+: R4.1, U1.52 (USB_DP)
/rp-core/USB_D-: R3.1, U1.51 (USB_DM)
/rp-core/VREG_AVDD: C19.2, R6.2, U1.46 (VREG_AVDD)
/rp-core/VREG_LX: L1.1, U1.48 (VREG_LX)
/rp-core/XIN: C5.2, U1.21 (XIN), U5.1
/rp-core/XOUT: R2.1, U1.22 (XOUT)
/rp-core/XOUT_Y: C6.2, R2.2, U5.3
GND: C5.1, C6.1, C7.1, C8.1, C9.1, C10.1, C11.1, C12.1, C13.1, C14.1, C15.1, C16.1, C17.1, C18.1, C19.1, Q3.2 (E), Q4.2 (E), SW3.2, SW4.2, TP1.1, U1.47 (VREG_PGND), U1.61 (GND), U5.2 (G), U5.4 (G); also elsewhere on the board

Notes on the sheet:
Supplies (RP2350 datasheet): IOVDD, QSPI_IOVDD, USB_OTP_VDD, ADC_AVDD and VREG_VIN on 3V3 (the buck, power sheet); the core regulator switches VREG_LX through 3.3 uH onto 1V1 (VREG_FB senses it), its analog supply VREG_AVDD through 27R / 4.7 uF. Capacitors as Yannick placed them, each drawn at the 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

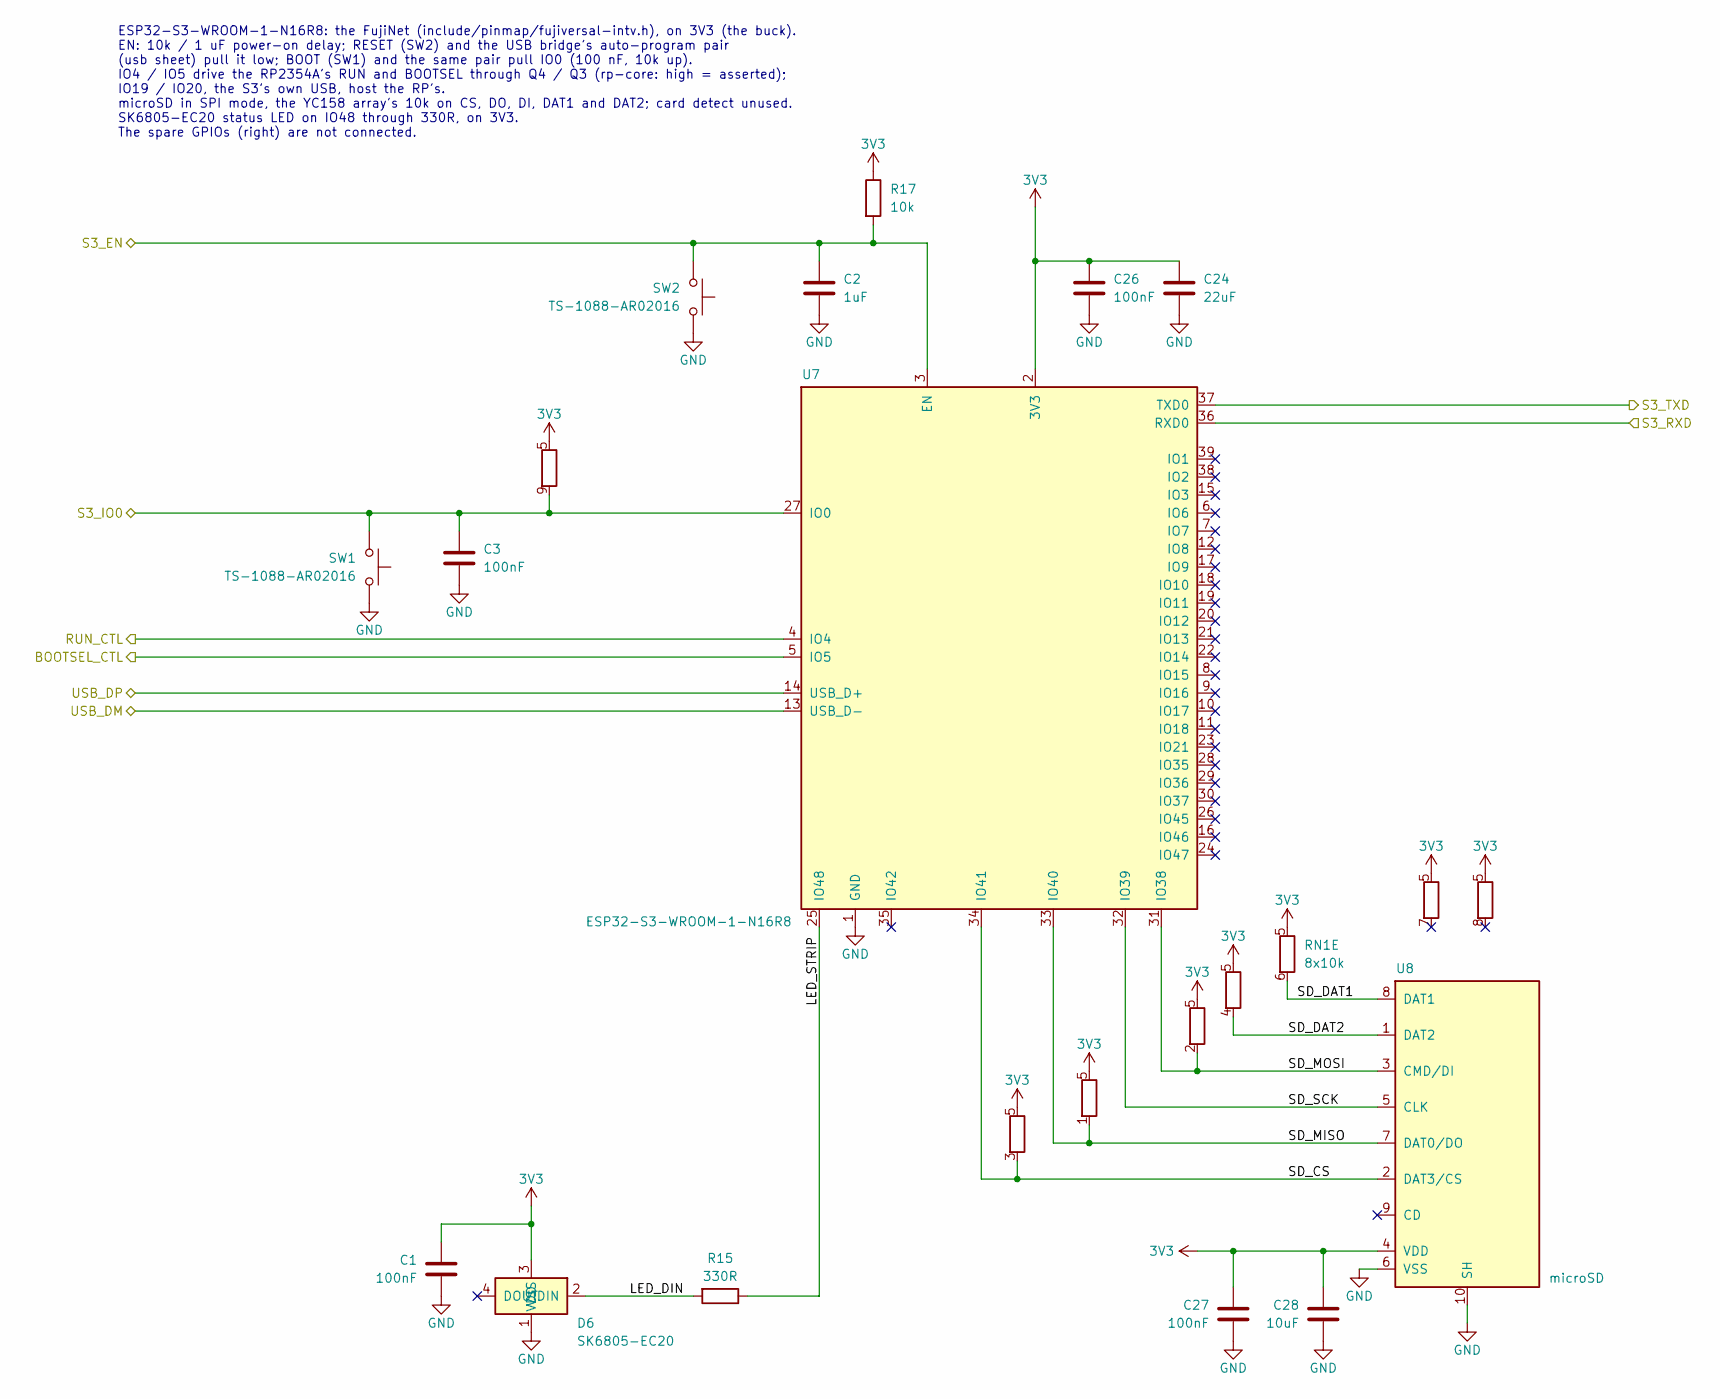
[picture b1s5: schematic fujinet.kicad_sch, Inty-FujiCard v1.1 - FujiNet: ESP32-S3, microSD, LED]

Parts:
C1, C3, C26, C27: 100nF; C0402; MPN CL05B104KO5NNNC; LCSC C1525
C2: 1uF; C0402; MPN CL05A105KA5NQNC; LCSC C52923
C24: 22uF; C0603; MPN CL10A226MQ8NRNC; LCSC C59461
C28: 10uF; C0603; MPN CL10A106KP8NNNC; LCSC C19702
D6: SK6805-EC20; LED-SMD_4P-L2.0-W2.0-TL_J-ST2020RGB-IC-P4-5-SO1; MPN SK6805-EC20; LCSC C2890036
R15: 330R; R0402; MPN 0402WGF3300TCE; LCSC C25104
R17: 10k; R0402; MPN 0402WGF1002TCE; LCSC C25744
RN1: 8x10k; RES-ARRAY-SMD_1206-L3.2-W1.6-P0.64; MPN YC158TJR-0710KL; LCSC C309679
SW1, SW2: TS-1088-AR02016; SW-SMD_L3.9-W3.0-P4.45; MPN TS-1088-AR02016; LCSC C720477
U7: ESP32-S3-WROOM-1-N16R8; WIRELM-SMD_ESP32-S3-WROOM-1; MPN ESP32-S3-WROOM-1-N16R8; LCSC C2913202
U8: microSD; SIM-SMD_LX_XDFP-0090-012; MPN TF-CARD-9P; LCSC C53144700

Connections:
3V3: C1.2, C24.2, C26.2, C27.2, C28.1, D6.3 (VDD), R17.1, RN1.5 (COM), RN1.10 (COM), U7.2 (3V3), U8.4 (VDD); also elsewhere on the board
/BOOTSEL_CTL: U7.5 (IO5); also elsewhere on the board
/RUN_CTL: U7.4 (IO4); also elsewhere on the board
/S3_EN: C2.2, R17.2, SW2.1, U7.3 (EN); also elsewhere on the board
/S3_IO0: C3.2, RN1.9 (R8), SW1.1, U7.27 (IO0); also elsewhere on the board
/S3_RXD: U7.36 (RXD0); also elsewhere on the board
/S3_TXD: U7.37 (TXD0); also elsewhere on the board
/USB_DM: U7.13 (USB_D-); also elsewhere on the board
/USB_DP: U7.14 (USB_D+); also elsewhere on the board
/fujinet/LED_DIN: D6.2 (DIN), R15.2
/fujinet/LED_STRIP: R15.1, U7.25 (IO48)
/fujinet/SD_CS: RN1.3 (R3), U7.34 (IO41), U8.2 (DAT3/CS)
/fujinet/SD_DAT1: RN1.6 (R5), U8.8 (DAT1)
/fujinet/SD_DAT2: RN1.4 (R4), U8.1 (DAT2)
/fujinet/SD_MISO: RN1.1 (R1), U7.33 (IO40), U8.7 (DAT0/DO)
/fujinet/SD_MOSI: RN1.2 (R2), U7.31 (IO38), U8.3 (CMD/DI)
/fujinet/SD_SCK: U7.32 (IO39), U8.5 (CLK)
GND: C1.1, C2.1, C3.1, C24.1, C26.1, C27.1, C28.2, D6.1 (VSS), SW1.2, SW2.2, U7.1 (GND), U7.40 (GND), U7.41 (GND), U8.6 (VSS), U8.10 (SH); also elsewhere on the board

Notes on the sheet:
ESP32-S3-WROOM-1-N16R8: the FujiNet (include/pinmap/fujiversal-intv.h), on 3V3 (the buck). EN: 10k / 1 uF power-on delay; RESET (SW2) and the USB bridge's auto-program pair (usb sheet) pull it low; BOOT (SW1) and the same pair pull IO0 (100 nF, 10k up). IO4 / IO5 drive the RP2354A's RUN and BOOTSEL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

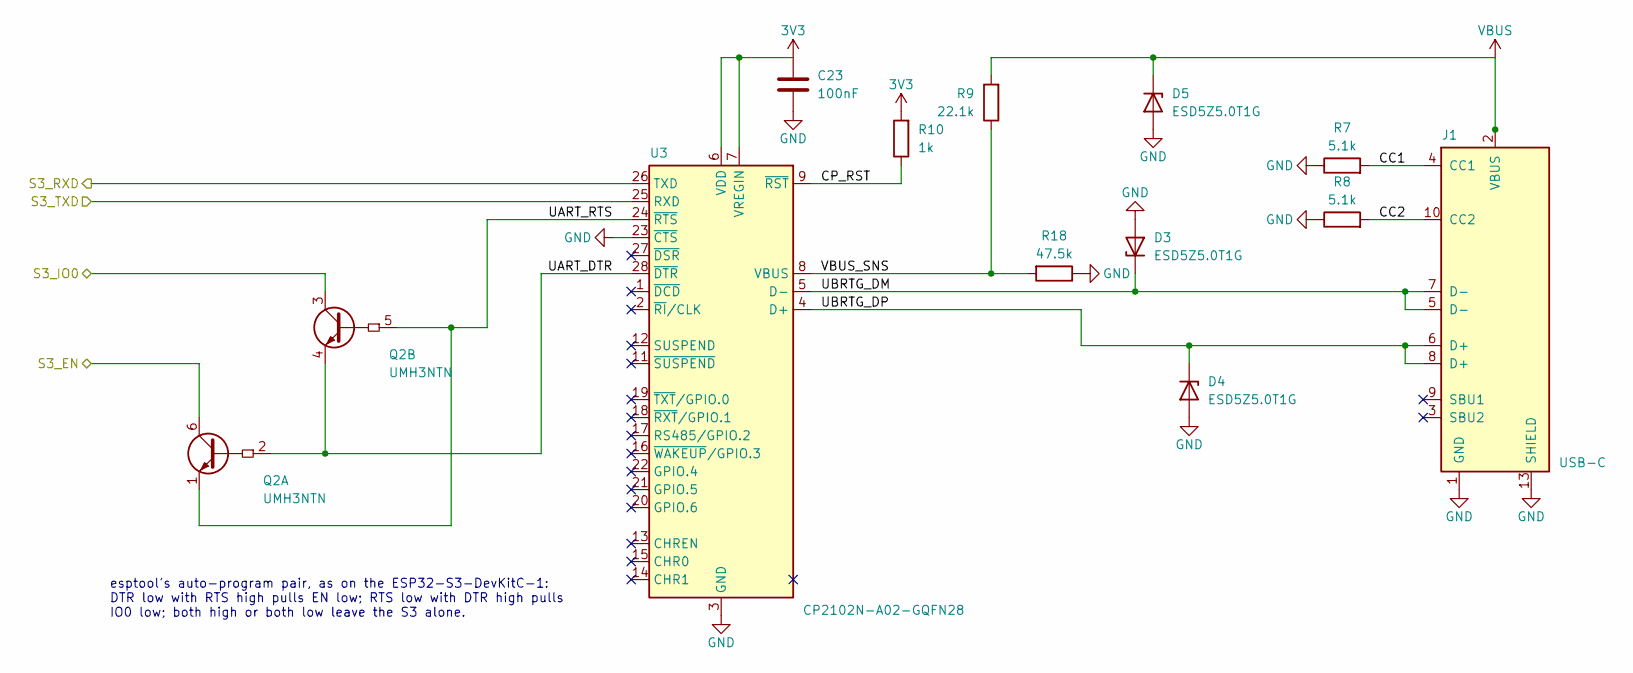
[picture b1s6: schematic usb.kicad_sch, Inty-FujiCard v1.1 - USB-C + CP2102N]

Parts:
C23: 100nF; C0402; MPN CL05B104KO5NNNC; LCSC C1525
D3, D4, D5: ESD5Z5.0T1G; SOD-523_L1.2-W0.8-LS1.6-RD; MPN ESD5Z5.0T1G; LCSC C343989
J1: USB-C; USB-C-SMD_TYPE-C-6PIN-2MD-073; MPN TYPE-C 16PIN 2MD(073); LCSC C2765186
Q2: UMH3NTN; SOT-363_L2.0-W1.3-P0.65-LS2.1-TL; MPN UMH3NTN; LCSC C123008
R7, R8: 5.1k; R0402; MPN 0402WGF5101TCE; LCSC C25905
R9: 22.1k; R0402; MPN AC0402FR-0722K1L; LCSC C226356
R10: 1k; R0402; MPN 0402WGF1001TCE; LCSC C11702
R18: 47.5k; R0402; MPN RC0402FR-0747K5L; LCSC C137974
U3: CP2102N-A02-GQFN28; QFN-28_L5.0-W5.0-P0.50-TL-EP3.3; MPN CP2102N-A02-GQFN28R; LCSC C964632

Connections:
3V3: C23.2, R10.2, U3.6 (VDD), U3.7 (VREGIN); also elsewhere on the board
/S3_EN: Q2.6 (C1); also elsewhere on the board
/S3_IO0: Q2.3 (C2); also elsewhere on the board
/S3_RXD: U3.26 (TXD); also elsewhere on the board
/S3_TXD: U3.25 (RXD); also elsewhere on the board
/usb/CC1: J1.4 (CC1), R7.2
/usb/CC2: J1.10 (CC2), R8.2
/usb/CP_RST: R10.1, U3.9 (~RST)
/usb/UART_DTR: Q2.2 (B1), Q2.4 (E2), U3.28 (~DTR)
/usb/UART_RTS: Q2.1 (E1), Q2.5 (B2), U3.24 (~RTS)
/usb/UBRTG_DM: D3.1 (K), J1.5 (D-), J1.7 (D-), U3.5 (D-)
/usb/UBRTG_DP: D4.1 (K), J1.6 (D+), J1.8 (D+), U3.4 (D+)
/usb/VBUS_SNS: R9.1, R18.2, U3.8 (VBUS)
GND: C23.1, D3.2 (A), D4.2 (A), D5.2 (A), J1.1 (GND), J1.12 (GND), J1.13 (SHIELD), J1.14 (SHIELD), R7.1, R8.1, R18.1, U3.3 (GND), U3.23 (~CTS), U3.29 (GND); also elsewhere on the board
VBUS: D5.1 (K), J1.2 (VBUS), J1.11 (VBUS), R9.2; also elsewhere on the board

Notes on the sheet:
esptool's auto-program pair, as on the ESP32-S3-DevKitC-1: DTR low with RTS high pulls EN low; RTS low with DTR high pulls IO0 low; both high or both low leave the S3 alone.

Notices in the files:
Astrocade/rev0/README.md:
Provenance and license:
- **Circuit blocks:** adapted from `FujiNet-INTV-Rev0` in this repository
(itself an adaptation of the PiNTY CARD, CERN-OHL-W-2.0) and the
ESP32-S3-DevKitC-1 v1.1 reference design.
- **Edge pinout:** Jay Tilton (ballyalley.com
`bally_technical_info_(cartridge_port).htm`), cross-checked against MCM
Design's modified cassette cartridge drawing.
- **Blade and physical data:** sakman55's Astrocade cartreader adapter
(github.com/sanni/cartreader discussion #354).
- **RP2350 regulator corner:** Raspberry Pi RP2350A minimal design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
